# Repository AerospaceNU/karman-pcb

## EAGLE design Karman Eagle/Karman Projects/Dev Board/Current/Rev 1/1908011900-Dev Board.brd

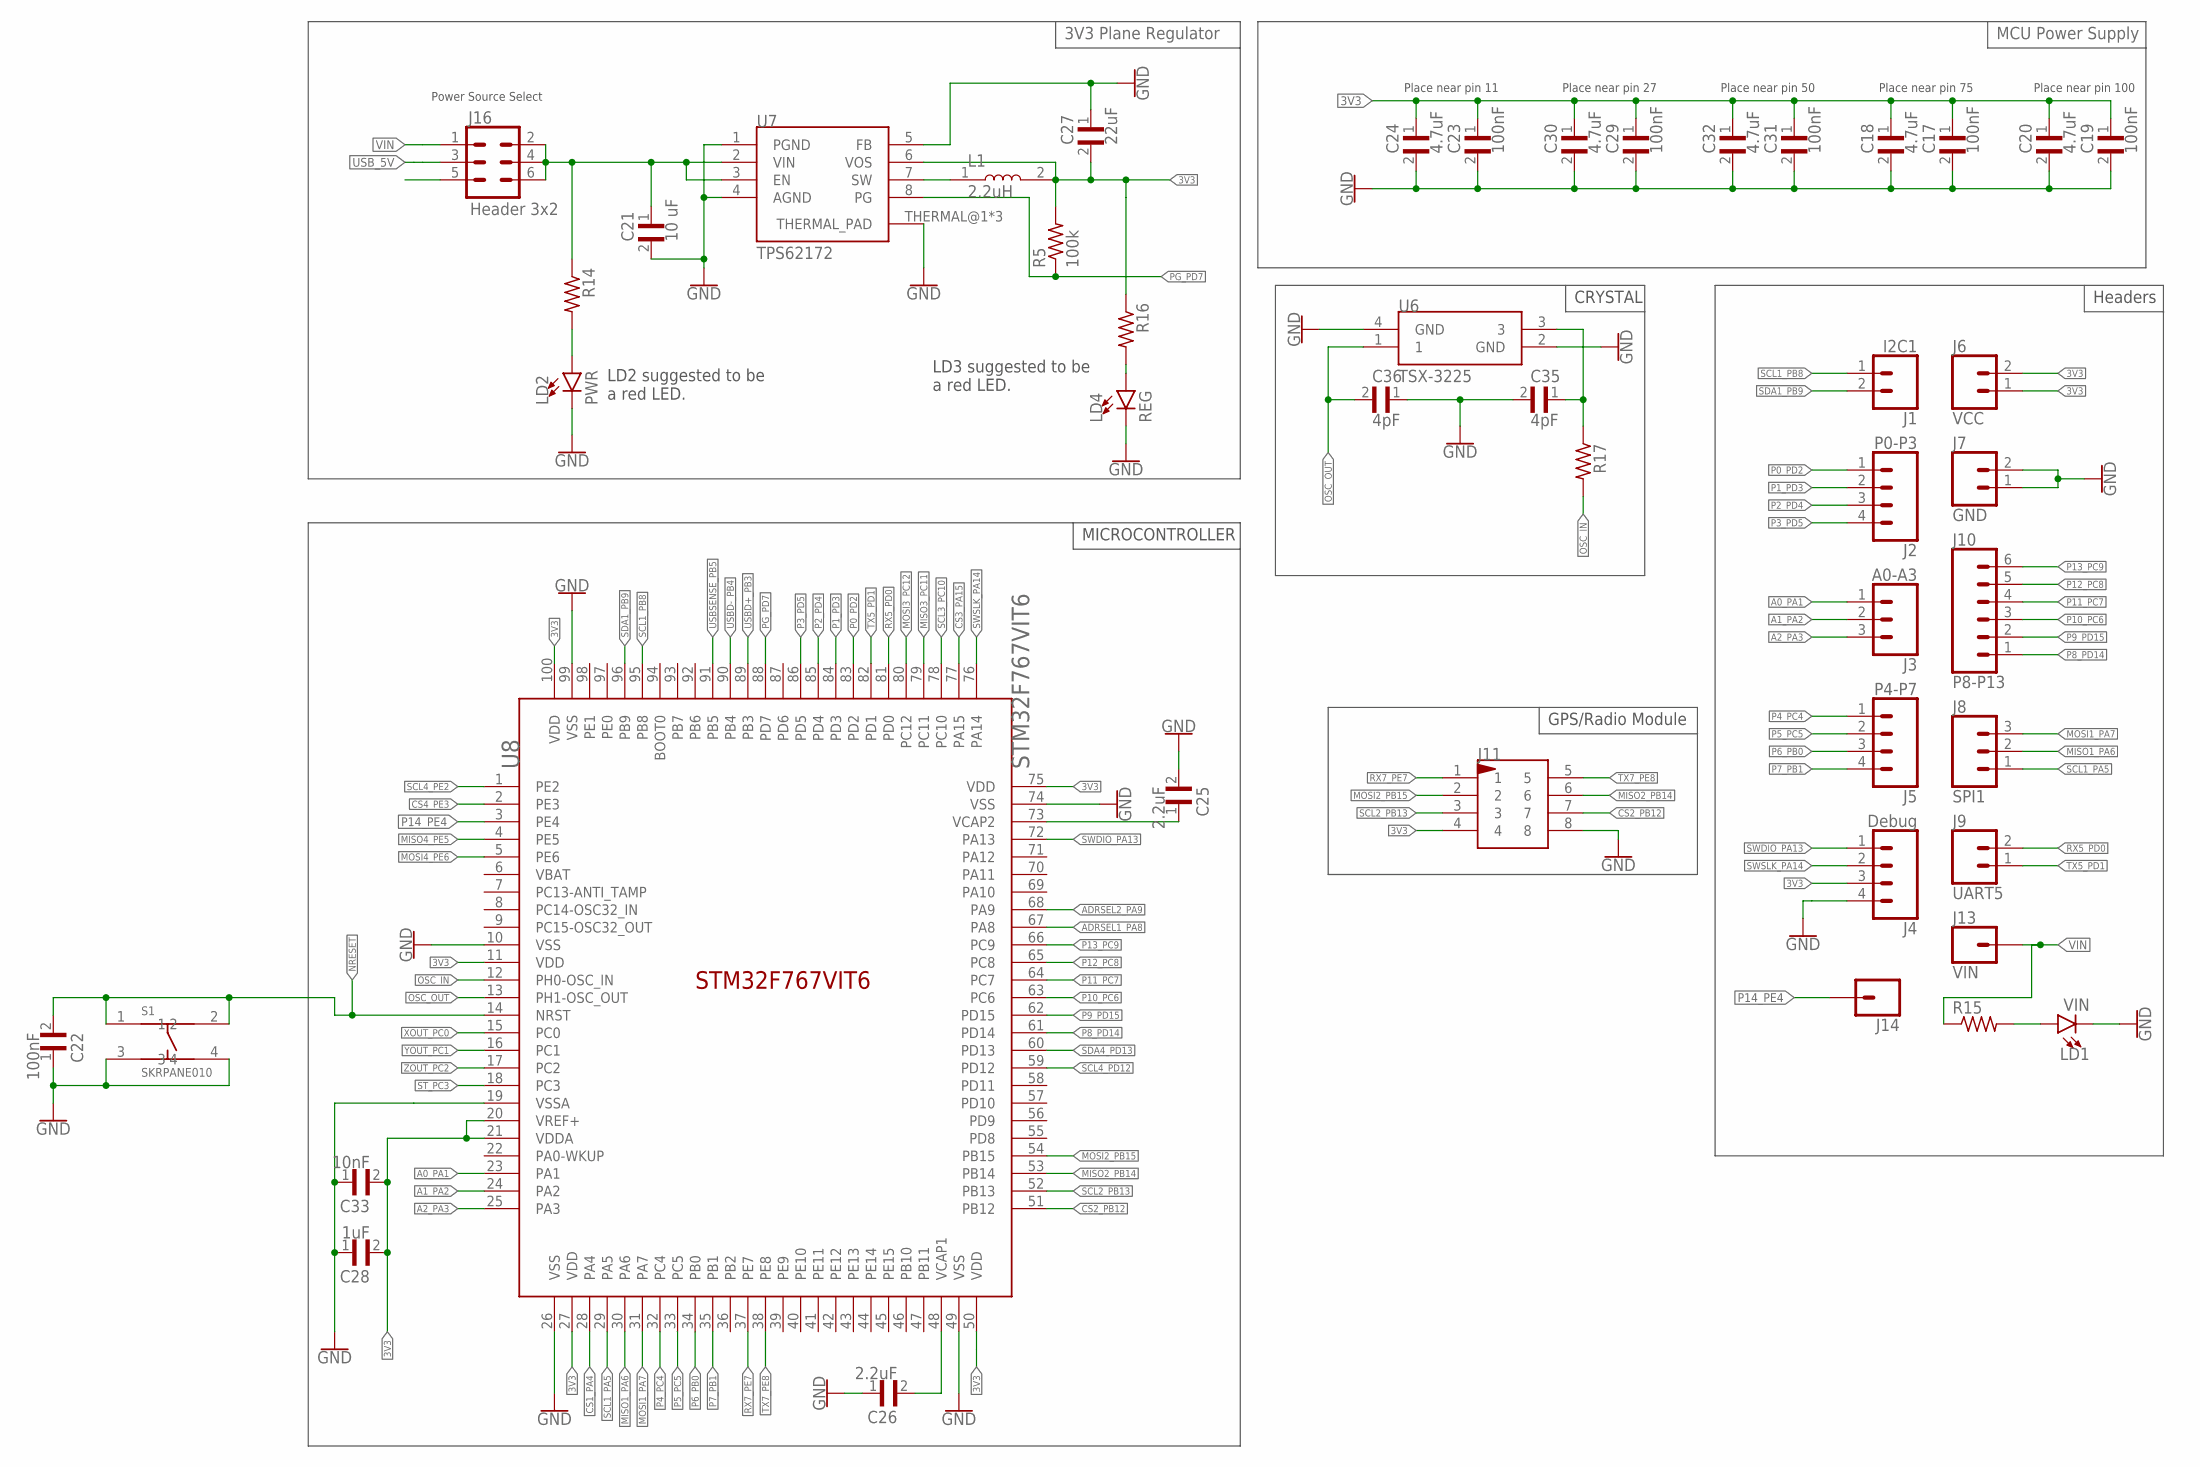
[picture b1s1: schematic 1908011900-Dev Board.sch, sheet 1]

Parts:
C17, C19, C22, C23, C29, C31: 100nF; CAPC1608X95N
C18, C20, C24, C30, C32: 4.7uF; CAPC1608X95N
C21: 10 uF; CAPC1608X95N
C25, C26: 2.2uF; CAPC1608X95N
C27: 22uF; CAPC1608X95N
C28: 1uF; CAPC1608X95N
C33: 10nF; CAPC1608X95N
C35, C36: 4pF; CAPC1608X95N
J1: I2C1; 1X02
J2: P0-P3; 1X04
J3: A0-A3; 1X03
J4: Debug; 1X04
J5: P4-P7; 1X04
J6: VCC; 1X02
J7: GND; 1X02
J8: SPI1; 1X03
J9: UART5; 1X02
J10: P8-P13; 1X06
J11: 087831-0819; 87831-0819
J13: VIN; 1X01
J14: CONN_01; 1X01
J16: Header 3x2; 2X3
L1: 2.2uH; INDC1608X95N
LD1: VIN; 0805_LED
LD2: PWR; 0805_LED
LD4: REG; 0805_LED
R5: 100k; RESC1608X50N
R14, R15, R16, R17: CRGH0603F221K; RESC1608X50N
S1: SKRPANE010
U6: TSX-3225
U7: TPS62172
U8: STM32F767VIT6; LQFP100_14X14

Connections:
3V3: C17.1, C18.1, C19.1, C20.1, C23.1, C24.1, C27.2, C28.2, C29.1, C30.1, C31.1, C32.1, C33.2, J4.3, J6.1, J6.2, J11.4, L1.2, R5.2, R16.1, U7.6 (VOS), U8.11 (VDD), U8.20 (VREF+), U8.21 (VDDA), U8.27 (VDD), U8.50 (VDD), U8.75 (VDD), U8.100 (VDD); also elsewhere on the board
A0_PA1: J3.1, U8.23 (PA1)
A1_PA2: J3.2, U8.24 (PA2)
A2_PA3: J3.3, U8.25 (PA3)
ADRSEL1_PA8: U8.67 (PA8); also elsewhere on the board
ADRSEL2_PA9: U8.68 (PA9); also elsewhere on the board
CS1_PA4: U8.28 (PA4); also elsewhere on the board
CS2_PB12: J11.7, U8.51 (PB12)
CS3_PA15: U8.77 (PA15); also elsewhere on the board
CS4_PE3: U8.2 (PE3); also elsewhere on the board
GND: C17.2, C18.2, C19.2, C20.2, C21.2, C22.1, C23.2, C24.2, C25.2, C26.1, C28.1, C29.2, C30.2, C31.2, C32.2, C33.1, C35.2, C36.1, J4.4, J7.1, J7.2, J11.8, LD1.C, LD2.C, LD4.C, S1.3, S1.4, U6.2 (GND), U6.4 (GND), U7.1 (PGND), U7.4 (AGND), U7.THERMAL@1 (THERMAL_PAD), U7.THERMAL@2 (THERMAL_PAD), U7.THERMAL@3 (THERMAL_PAD), U8.10 (VSS), U8.19 (VSSA), U8.26 (VSS), U8.49 (VSS), U8.74 (VSS), U8.99 (VSS); also elsewhere on the board
MISO1_PA6: J8.2, U8.30 (PA6); also elsewhere on the board
MISO2_PB14: J11.6, U8.53 (PB14)
MISO3_PC11: U8.79 (PC11); also elsewhere on the board
MISO4_PE5: U8.4 (PE5); also elsewhere on the board
MOSI1_PA7: J8.3, U8.31 (PA7); also elsewhere on the board
MOSI2_PB15: J11.2, U8.54 (PB15)
MOSI3_PC12: U8.80 (PC12); also elsewhere on the board
MOSI4_PE6: U8.5 (PE6); also elsewhere on the board
unnamed: C25.1, U8.73 (VCAP2)
unnamed: C26.2, U8.48 (VCAP1)
unnamed: L1.1, U7.7 (SW)
unnamed: LD1.A, R15.2
unnamed: LD2.A, R14.2
unnamed: C27.1, U7.5 (FB)
unnamed: C35.1, R17.1, U6.3
unnamed: C21.1, J16.2, J16.4, J16.6, R14.1, U7.2 (VIN), U7.3 (EN)
unnamed: LD4.A, R16.2
NRESET: C22.2, S1.1, S1.2, U8.14 (NRST); also elsewhere on the board
OSC_IN: R17.2, U8.12 (PH0-OSC_IN)
OSC_OUT: C36.2, U6.1, U8.13 (PH1-OSC_OUT)
P0_PD2: J2.1, U8.83 (PD2)
P1_PD3: J2.2, U8.84 (PD3)
P2_PD4: J2.3, U8.85 (PD4)
P3_PD5: J2.4, U8.86 (PD5)
P4_PC4: J5.1, U8.32 (PC4)
P5_PC5: J5.2, U8.33 (PC5)
P6_PB0: J5.3, U8.34 (PB0)
P7_PB1: J5.4, U8.35 (PB1)
P8_PD14: J10.1, U8.61 (PD14)
P9_PD15: J10.2, U8.62 (PD15)
P10_PC6: J10.3, U8.63 (PC6)
P11_PC7: J10.4, U8.64 (PC7)
P12_PC8: J10.5, U8.65 (PC8)
P13_PC9: J10.6, U8.66 (PC9)
P14_PE4: J14.1, U8.3 (PE4)
PG_PD7: R5.1, U7.8 (PG), U8.88 (PD7)
RX5_PD0: J9.2, U8.81 (PD0)
RX7_PE7: J11.1, U8.37 (PE7)
SCL1_PA5: J8.1, U8.29 (PA5); also elsewhere on the board
SCL1_PB8: J1.1, U8.95 (PB8); also elsewhere on the board
SCL2_PB13: J11.3, U8.52 (PB13)
SCL3_PC10: U8.78 (PC10); also elsewhere on the board
SCL4_PD12: U8.59 (PD12); also elsewhere on the board
SCL4_PE2: U8.1 (PE2); also elsewhere on the board
SDA1_PB9: J1.2, U8.96 (PB9); also elsewhere on the board
SDA4_PD13: U8.60 (PD13); also elsewhere on the board
ST_PC3: U8.18 (PC3); also elsewhere on the board
SWDIO_PA13: J4.1, U8.72 (PA13)
SWSLK_PA14: J4.2, U8.76 (PA14)
TX5_PD1: J9.1, U8.82 (PD1)
TX7_PE8: J11.5, U8.38 (PE8)
USBD+_PB3: U8.89 (PB3); also elsewhere on the board
USBD-_PB4: U8.90 (PB4); also elsewhere on the board
USBSENSE_PB5: U8.91 (PB5); also elsewhere on the board
USB_5V: J16.3; also elsewhere on the board
VIN: J13.1, J16.1, R15.1
XOUT_PC0: U8.15 (PC0); also elsewhere on the board
YOUT_PC1: U8.16 (PC1); also elsewhere on the board
ZOUT_PC2: U8.17 (PC2); also elsewhere on the board

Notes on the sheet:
MICROCONTROLLER
Headers
Place near pin 11
Place near pin 27
Place near pin 50
Place near pin 75
Place near pin 100
GPS/Radio Module
MCU Power Supply
3V3 Plane Regulator
CRYSTAL
Power Source Select
LD2 suggested to be a red LED.
LD3 suggested to be a red LED.

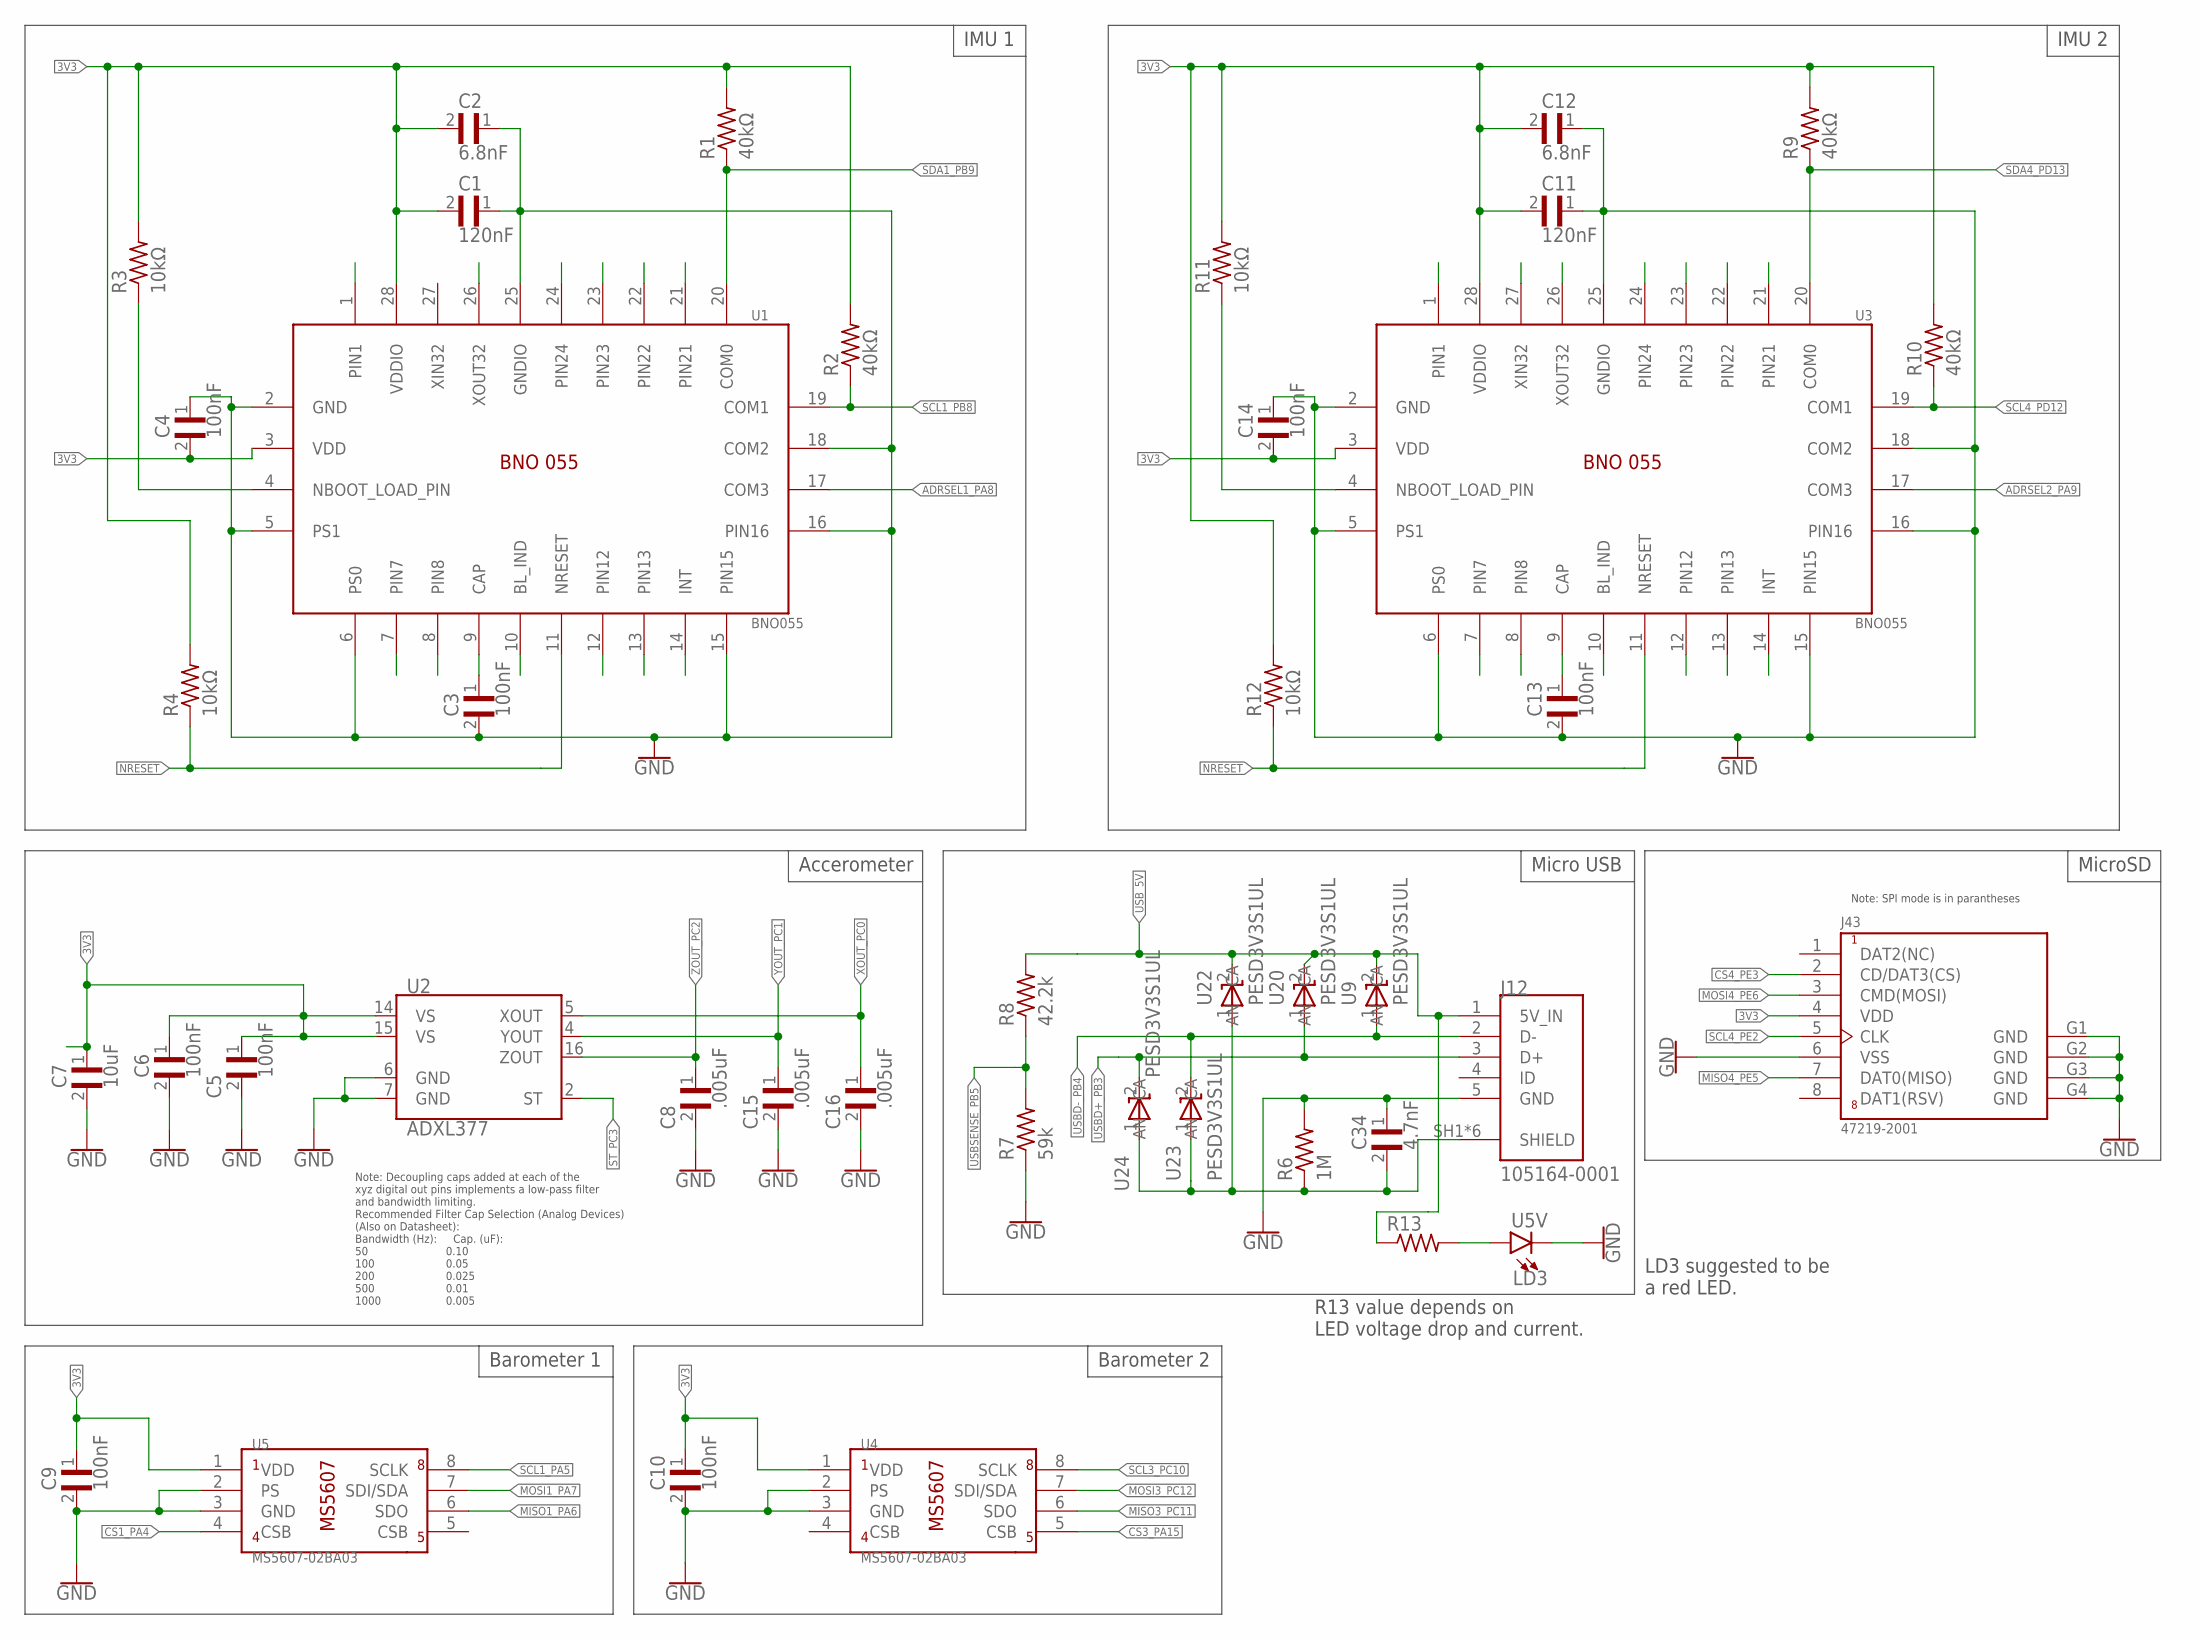
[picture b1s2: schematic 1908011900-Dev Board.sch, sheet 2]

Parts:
C1, C11: 120nF; CAPC1608X95N
C2, C12: 6.8nF; CAPC1608X95N
C3, C4, C5, C6, C9, C10, C13, C14: 100nF; CAPC1608X95N
C7: 10uF; CAPC1608X95N
C8, C15, C16: .005uF; CAPC1608X95N
C34: 4.7nF; CAPC1608X95N
J12: 105164-0001; MOLEX_105164-0001
J43: 47219-2001; MOLEX_47219-2001
LD3: U5V; 0805_LED
R1, R2, R9, R10: 40kΩ; RESC1608X50N
R3, R4, R11, R12: 10kΩ; RESC1608X50N
R6: 1M; RESC1608X50N
R7: 59k; RESC1608X50N
R8: 42.2k; RESC1608X50N
R13: CRGH0603F221K; RESC1608X50N
U1, U3: BNO055; LGA28R50P4X10_380X520X100
U2: ADXL377; LFCSP-16-3X3
U4, U5: MS5607-02BA03; TE_MS860702BA01-50
U9, U20, U22, U23, U24: PESD3V3S1UL; SOD882

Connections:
3V3: C1.2, C2.2, C4.2, C5.1, C6.1, C7.1, C9.1, C10.1, C11.2, C12.2, C14.2, J43.4 (VDD), R1.2, R2.2, R3.2, R4.2, R9.2, R10.2, R11.2, R12.2, U1.3 (VDD), U1.28 (VDDIO), U2.14 (VS), U2.15 (VS), U3.3 (VDD), U3.28 (VDDIO), U4.1 (VDD), U5.1 (VDD); also elsewhere on the board
ADRSEL1_PA8: U1.17 (COM3); also elsewhere on the board
ADRSEL2_PA9: U3.17 (COM3); also elsewhere on the board
CS1_PA4: U5.4 (CSB); also elsewhere on the board
CS3_PA15: U4.5 (CSB); also elsewhere on the board
CS4_PE3: J43.2 (CD/DAT3(CS)); also elsewhere on the board
GND: C1.1, C2.1, C3.2, C4.1, C5.2, C6.2, C7.2, C8.2, C9.2, C10.2, C11.1, C12.1, C13.2, C14.1, C15.2, C16.2, C34.1, J12.5 (GND), J43.6 (VSS), J43.G1 (GND), J43.G2 (GND), J43.G3 (GND), J43.G4 (GND), LD3.C, R6.2, R7.1, U1.2 (GND), U1.5 (PS1), U1.6 (PS0), U1.15 (PIN15), U1.16 (PIN16), U1.18 (COM2), U1.25 (GNDIO), U2.6 (GND), U2.7 (GND), U3.2 (GND), U3.5 (PS1), U3.6 (PS0), U3.15 (PIN15), U3.16 (PIN16), U3.18 (COM2), U3.25 (GNDIO), U4.2 (PS), U4.3 (GND), U5.2 (PS), U5.3 (GND); also elsewhere on the board
MISO1_PA6: U5.6 (SDO); also elsewhere on the board
MISO3_PC11: U4.6 (SDO); also elsewhere on the board
MISO4_PE5: J43.7 (DAT0(MISO)); also elsewhere on the board
MOSI1_PA7: U5.7 (SDI/SDA); also elsewhere on the board
MOSI3_PC12: U4.7 (SDI/SDA); also elsewhere on the board
MOSI4_PE6: J43.3 (CMD(MOSI)); also elsewhere on the board
unnamed: C3.1, U1.9 (CAP)
unnamed: R3.1, U1.4 (NBOOT_LOAD_PIN)
unnamed: C13.1, U3.9 (CAP)
unnamed: R11.1, U3.4 (NBOOT_LOAD_PIN)
unnamed: C34.2, J12.SH1 (SHIELD), J12.SH2 (SHIELD), J12.SH3 (SHIELD), J12.SH4 (SHIELD), J12.SH5 (SHIELD), J12.SH6 (SHIELD), R6.1, U22.1 (CA), U23.1 (CA), U24.1 (CA)
unnamed: LD3.A, R13.2
NRESET: R4.1, R12.1, U1.11 (NRESET), U3.11 (NRESET); also elsewhere on the board
SCL1_PA5: U5.8 (SCLK); also elsewhere on the board
SCL1_PB8: R2.1, U1.19 (COM1); also elsewhere on the board
SCL3_PC10: U4.8 (SCLK); also elsewhere on the board
SCL4_PD12: R10.1, U3.19 (COM1); also elsewhere on the board
SCL4_PE2: J43.5 (CLK); also elsewhere on the board
SDA1_PB9: R1.1, U1.20 (COM0); also elsewhere on the board
SDA4_PD13: R9.1, U3.20 (COM0); also elsewhere on the board
ST_PC3: U2.2 (ST); also elsewhere on the board
USBD+_PB3: J12.3 (D+), U20.1 (CA), U24.2 (AN); also elsewhere on the board
USBD-_PB4: J12.2 (D-), U9.1 (CA), U23.2 (AN); also elsewhere on the board
USBSENSE_PB5: R7.2, R8.1; also elsewhere on the board
USB_5V: J12.1 (5V_IN), R8.2, R13.1, U9.2 (AN), U20.2 (AN), U22.2 (AN); also elsewhere on the board
XIN32: U1.27 (XIN32)
XOUT_PC0: C16.1, U2.5 (XOUT); also elsewhere on the board
YOUT_PC1: C15.1, U2.4 (YOUT); also elsewhere on the board
ZOUT_PC2: C8.1, U2.16 (ZOUT); also elsewhere on the board

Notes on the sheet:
IMU 1
IMU 2
Note: Decoupling caps added at each of the xyz digital out pins implements a low-pass filter and bandwidth limiting. Recommended Filter Cap Selection (Analog Devices) (Also on Datasheet): Bandwidth (Hz): Cap. (uF): 50 0.10 100 0.05 200 0.025 500 0.01 1000 0.005
Accerometer
Micro USB
Barometer 1
Barometer 2
MicroSD
R13 value depends on LED voltage drop and current.
LD3 suggested to be a red LED.

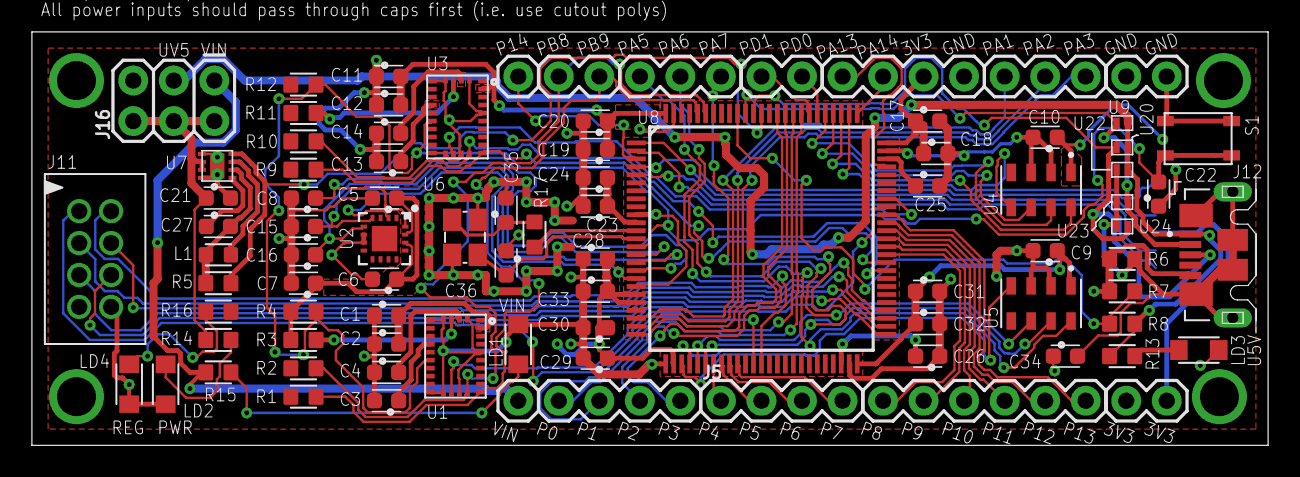
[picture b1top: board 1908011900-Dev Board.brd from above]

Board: 2 copper layers, 77.5 x 25.9 mm, 88 parts (1 on the bottom side), 76 nets.

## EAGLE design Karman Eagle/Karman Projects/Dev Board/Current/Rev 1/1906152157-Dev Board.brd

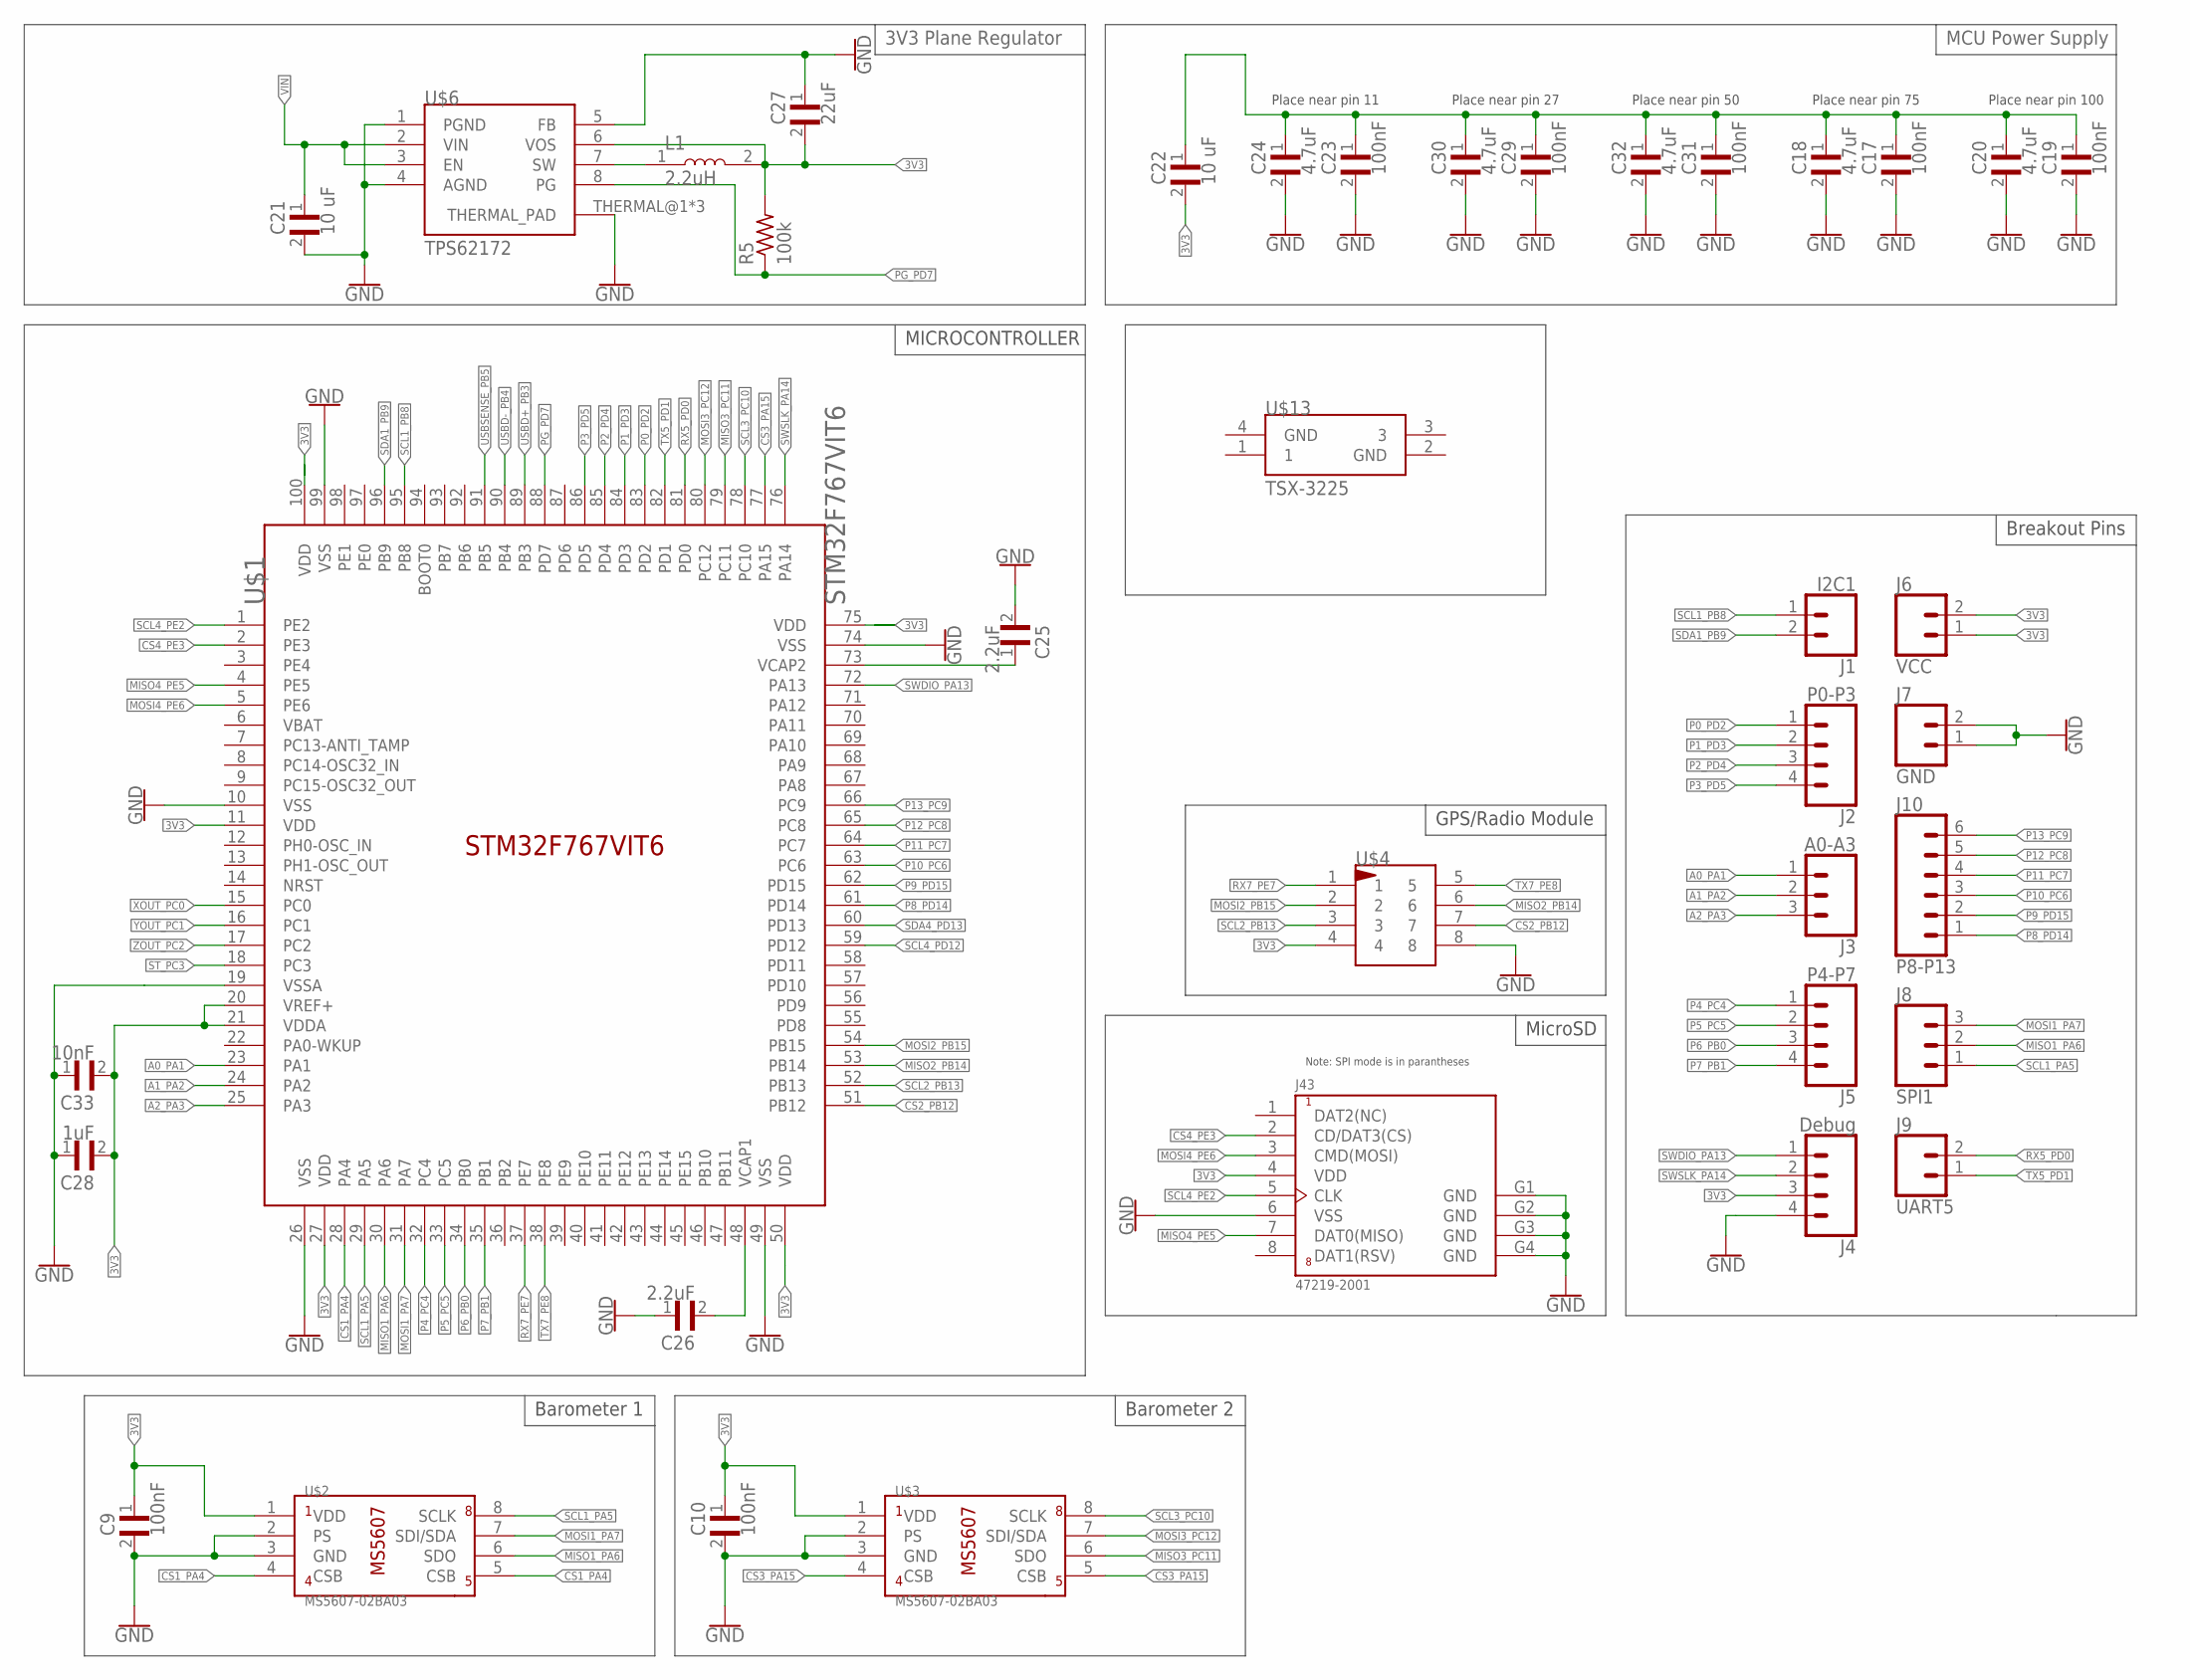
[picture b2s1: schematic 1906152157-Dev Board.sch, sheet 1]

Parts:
C9, C10, C17, C19, C23, C29, C31: 100nF; CAPC1608X95N
C18, C20, C24, C30, C32: 4.7uF; CAPC1608X95N
C21, C22: 10 uF; CAPC1608X95N
C25, C26: 2.2uF; CAPC1608X95N
C27: 22uF; CAPC1608X95N
C28: 1uF; CAPC1608X95N
C33: 10nF; CAPC1608X95N
J1: I2C1; 1X02
J2: P0-P3; 1X04
J3: A0-A3; 1X03
J4: Debug; 1X04
J5: P4-P7; 1X04
J6: VCC; 1X02
J7: GND; 1X02
J8: SPI1; 1X03
J9: UART5; 1X02
J10: P8-P13; 1X06_LOCK
J43: 47219-2001; MOLEX_47219-2001
L1: 2.2uH; INDC1608X95N
R5: 100k; RESC1608X50N
U$1: STM32F767VIT6; LQFP100_14X14
U$2, U$3: MS5607-02BA03; TE_MS860702BA01-50
U$4: 087831-0819; 87831-0819
U$6: TPS62172
U$13: TSX-3225

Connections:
3V3: C9.1, C10.1, C22.2, C27.2, C28.2, C33.2, J4.3, J6.1, J6.2, J43.4 (VDD), L1.2, R5.2, U$1.11 (VDD), U$1.20 (VREF+), U$1.21 (VDDA), U$1.27 (VDD), U$1.50 (VDD), U$1.75 (VDD), U$1.100 (VDD), U$2.1 (VDD), U$3.1 (VDD), U$4.4, U$6.6 (VOS)
A0_PA1: J3.1, U$1.23 (PA1)
A1_PA2: J3.2, U$1.24 (PA2)
A2_PA3: J3.3, U$1.25 (PA3)
CS1_PA4: U$1.28 (PA4), U$2.4 (CSB), U$2.5 (CSB)
CS2_PB12: U$1.51 (PB12), U$4.7
CS3_PA15: U$1.77 (PA15), U$3.4 (CSB), U$3.5 (CSB)
CS4_PE3: J43.2 (CD/DAT3(CS)), U$1.2 (PE3)
GND: C9.2, C10.2, C17.2, C18.2, C19.2, C20.2, C21.2, C23.2, C24.2, C25.2, C26.1, C27.1, C28.1, C29.2, C30.2, C31.2, C32.2, C33.1, J4.4, J7.1, J7.2, J43.6 (VSS), J43.G1 (GND), J43.G2 (GND), J43.G3 (GND), J43.G4 (GND), U$1.10 (VSS), U$1.19 (VSSA), U$1.26 (VSS), U$1.49 (VSS), U$1.74 (VSS), U$1.99 (VSS), U$2.2 (PS), U$2.3 (GND), U$3.2 (PS), U$3.3 (GND), U$4.8, U$6.1 (PGND), U$6.4 (AGND), U$6.5 (FB), U$6.THERMAL@1 (THERMAL_PAD), U$6.THERMAL@2 (THERMAL_PAD), U$6.THERMAL@3 (THERMAL_PAD); also elsewhere on the board
MISO1_PA6: J8.2, U$1.30 (PA6), U$2.6 (SDO)
MISO2_PB14: U$1.53 (PB14), U$4.6
MISO3_PC11: U$1.79 (PC11), U$3.6 (SDO)
MISO4_PE5: J43.7 (DAT0(MISO)), U$1.4 (PE5)
MOSI1_PA7: J8.3, U$1.31 (PA7), U$2.7 (SDI/SDA)
MOSI2_PB15: U$1.54 (PB15), U$4.2
MOSI3_PC12: U$1.80 (PC12), U$3.7 (SDI/SDA)
MOSI4_PE6: J43.3 (CMD(MOSI)), U$1.5 (PE6)
unnamed: C25.1, U$1.73 (VCAP2)
unnamed: C26.2, U$1.48 (VCAP1)
unnamed: L1.1, U$6.7 (SW)
unnamed: C17.1, C18.1, C19.1, C20.1, C22.1, C23.1, C24.1, C29.1, C30.1, C31.1, C32.1
P0_PD2: J2.1, U$1.83 (PD2)
P1_PD3: J2.2, U$1.84 (PD3)
P2_PD4: J2.3, U$1.85 (PD4)
P3_PD5: J2.4, U$1.86 (PD5)
P4_PC4: J5.1, U$1.32 (PC4)
P5_PC5: J5.2, U$1.33 (PC5)
P6_PB0: J5.3, U$1.34 (PB0)
P7_PB1: J5.4, U$1.35 (PB1)
P8_PD14: J10.1, U$1.61 (PD14)
P9_PD15: J10.2, U$1.62 (PD15)
P10_PC6: J10.3, U$1.63 (PC6)
P11_PC7: J10.4, U$1.64 (PC7)
P12_PC8: J10.5, U$1.65 (PC8)
P13_PC9: J10.6, U$1.66 (PC9)
PG_PD7: R5.1, U$1.88 (PD7), U$6.8 (PG)
RX5_PD0: J9.2, U$1.81 (PD0)
RX7_PE7: U$1.37 (PE7), U$4.1
SCL1_PA5: J8.1, U$1.29 (PA5), U$2.8 (SCLK)
SCL1_PB8: J1.1, U$1.95 (PB8); also elsewhere on the board
SCL2_PB13: U$1.52 (PB13), U$4.3
SCL3_PC10: U$1.78 (PC10), U$3.8 (SCLK)
SCL4_PD12: U$1.59 (PD12); also elsewhere on the board
SCL4_PE2: J43.5 (CLK), U$1.1 (PE2)
SDA1_PB9: J1.2, U$1.96 (PB9); also elsewhere on the board
SDA4_PD13: U$1.60 (PD13); also elsewhere on the board
ST_PC3: U$1.18 (PC3); also elsewhere on the board
SWDIO_PA13: J4.1, U$1.72 (PA13)
SWSLK_PA14: J4.2, U$1.76 (PA14)
TX5_PD1: J9.1, U$1.82 (PD1)
TX7_PE8: U$1.38 (PE8), U$4.5
USBD+_PB3: U$1.89 (PB3); also elsewhere on the board
USBD-_PB4: U$1.90 (PB4); also elsewhere on the board
USBSENSE_PB5: U$1.91 (PB5); also elsewhere on the board
VIN: C21.1, U$6.2 (VIN), U$6.3 (EN); also elsewhere on the board
XOUT_PC0: U$1.15 (PC0); also elsewhere on the board
YOUT_PC1: U$1.16 (PC1); also elsewhere on the board
ZOUT_PC2: U$1.17 (PC2); also elsewhere on the board

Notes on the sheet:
MICROCONTROLLER
Barometer 1
Barometer 2
Breakout Pins
Place near pin 11
Place near pin 27
Place near pin 50
Place near pin 75
Place near pin 100
GPS/Radio Module
MicroSD
MCU Power Supply
3V3 Plane Regulator

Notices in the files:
parts and their libraries:
SparkFun-Connectors: Licensing: Creative Commons ShareAlike 4.0 International - https://creativecommons.org/licenses/by-sa/4.0
